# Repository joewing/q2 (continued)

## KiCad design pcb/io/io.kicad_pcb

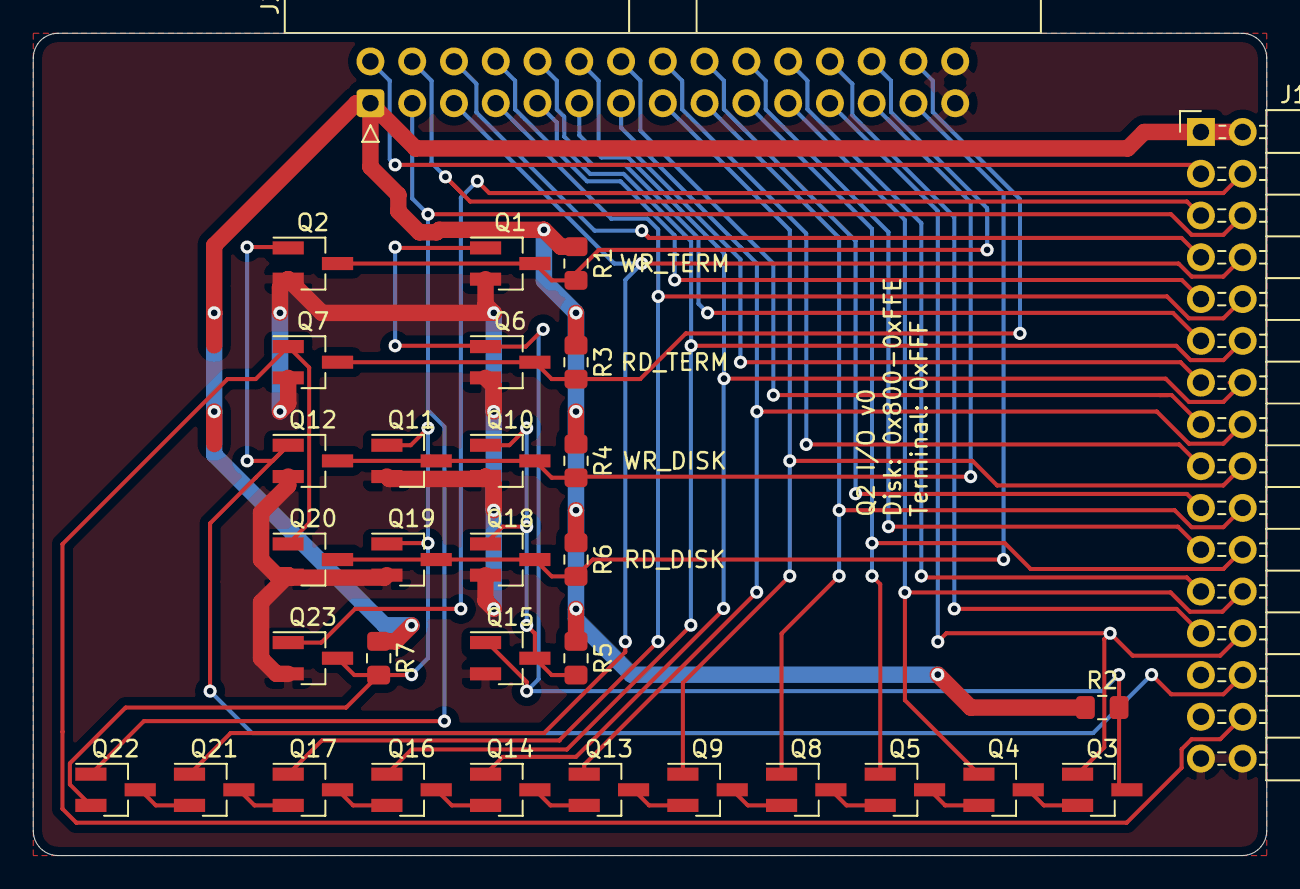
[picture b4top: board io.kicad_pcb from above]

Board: 2 copper layers, 75.0 x 50.0 mm, 32 parts (0 on the bottom side), 45 nets.

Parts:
J1: Main; PinHeader_2x16_P2.54mm_Horizontal
J2: Disk; IDC-Header_2x15_P2.54mm_Horizontal
Q1, Q2, Q3, Q4, Q5, Q6, Q7, Q8, Q9, Q10, Q11, Q12, Q13, Q14, Q15, Q16, Q17, Q18, Q19, Q20, Q21, Q22, Q23: 2N7002; SOT-23_Handsoldering
R1, R2, R3, R4, R5, R6, R7: 10k; R_0805_2012Metric_Pad1.15x1.40mm_HandSolder

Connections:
A0: J1.26, J2.23, Q3.1
A1: J1.24, J2.21, Q4.1
A2: J1.22, J2.19, Q5.1
A3: J1.20, J2.17, Q8.1
A4: J1.18, J2.15, Q9.1
A5: J1.16, J2.13, Q13.1
A6: J1.14, J2.11, Q14.1
A7: J1.12, J2.9, Q16.1
A8: J1.10, J2.7, Q17.1
A9: J1.8, J2.5, Q21.1
A10: J1.6, J2.3, Q22.1
A11: J1.4, Q23.1
D0: J1.25, J2.24
D1: J1.23, J2.22
D2: J1.21, J2.20
D3: J1.19, J2.18
D4: J1.17, J2.16
D5: J1.15, J2.14
D6: J1.13, J2.12
D7: J1.11, J2.10
D8: J1.9, J2.8
D9: J1.7, J2.6
D10: J1.5, J2.4
D11: J1.3, J2.2
GND: J1.31, J1.32, J2.29, J2.30, Q1.2, Q2.2, Q6.2, Q7.2, Q10.2, Q11.2, Q12.2, Q15.2, Q18.2, Q19.2, Q20.2, Q23.2
unnamed: Q1.1, Q3.3, Q6.1, Q15.1, R2.2
unnamed: Q3.2, Q4.3
unnamed: Q4.2, Q5.3
unnamed: Q5.2, Q8.3
unnamed: Q8.2, Q9.3
unnamed: Q10.1, Q15.3, Q18.1, R5.2
unnamed: Q13.2, Q14.3
unnamed: Q9.2, Q13.3
unnamed: Q14.2, Q16.3
unnamed: Q16.2, Q17.3
unnamed: Q17.2, Q21.3
unnamed: Q21.2, Q22.3
RD_DISK: J2.27, Q18.3, Q19.3, Q20.3, R6.2
RD_TERM: J2.28, Q6.3, Q7.3, R3.2
VCC: J1.1, J1.2, J2.1, R1.1, R2.1, R3.1, R4.1, R5.1, R6.1, R7.1
WR_DISK: J2.25, Q10.3, Q11.3, Q12.3, R4.2
WR_TERM: J2.26, Q1.3, Q2.3, R1.2
~A11: Q11.1, Q19.1, Q22.2, Q23.3, R7.2
~RDM: J1.30, Q7.1, Q20.1
~WRM: J1.28, Q2.1, Q12.1

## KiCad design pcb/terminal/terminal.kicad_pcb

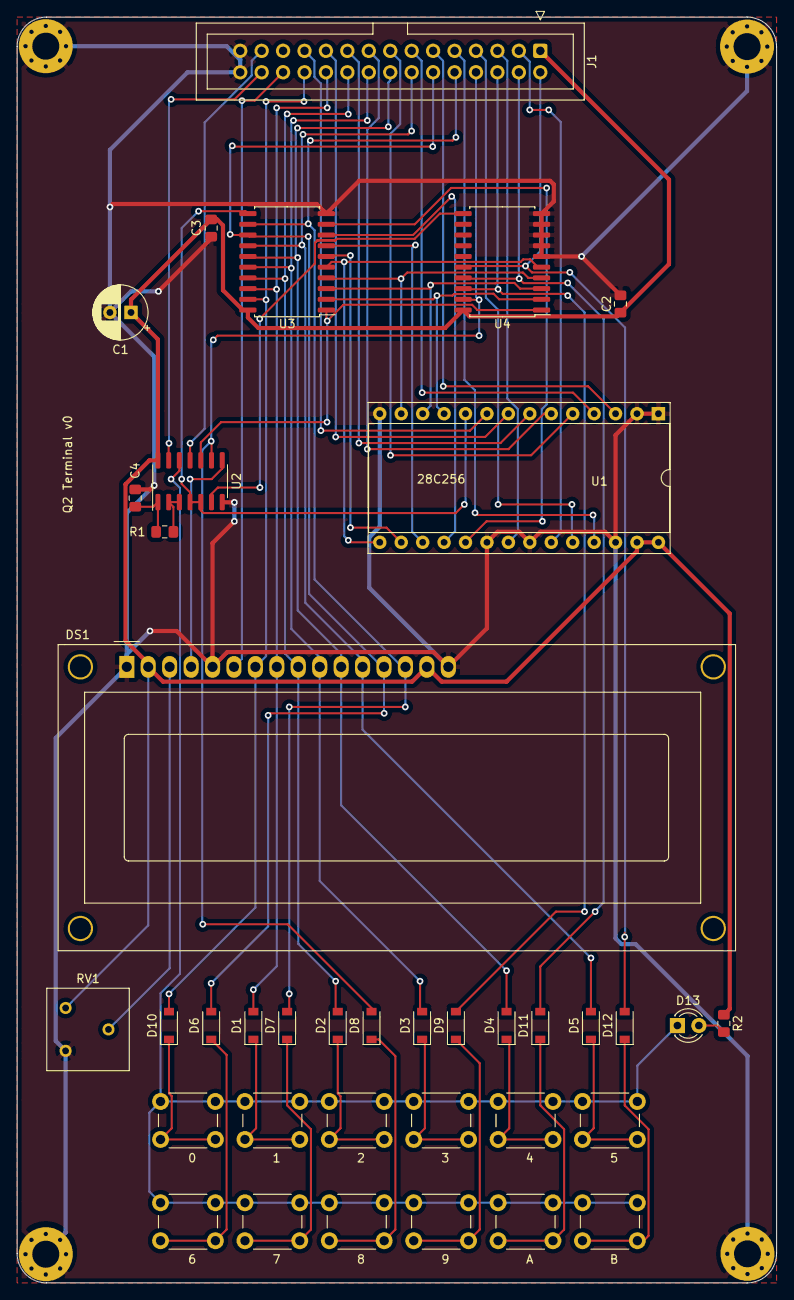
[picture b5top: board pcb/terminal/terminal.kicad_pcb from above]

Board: 2 copper layers, 90.0 x 150.0 mm, 42 parts (0 on the bottom side), 57 nets.

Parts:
C1: 47u; CP_Radial_D6.3mm_P2.50mm
C2, C3, C4: 0.1u; C_0805_2012Metric_Pad1.15x1.40mm_HandSolder
D1, D2, D3, D4, D5, D6, D7, D8, D9, D10, D11, D12: 1N4148; D_SOD-123
D13: LED; LED_D3.0mm
DS1: WC1602A
H1, H2, H3, H4: MountingHole_Pad; MountingHole_3.2mm_M3_Pad_Via
J1: Conn_02x15_Odd_Even; IDC-Header_2x15_P2.54mm_Vertical
R1: 1k; R_0805_2012Metric_Pad1.15x1.40mm_HandSolder
R2: 10k; R_0805_2012Metric_Pad1.15x1.40mm_HandSolder
RV1: 10k; Potentiometer_Bourns_3386F_Vertical
SW1: 1; SW_PUSH_6mm
SW2: 2; SW_PUSH_6mm
SW3: 3; SW_PUSH_6mm
SW4: A; SW_PUSH_6mm
SW5: 4; SW_PUSH_6mm
SW6: 5; SW_PUSH_6mm
SW7: 6; SW_PUSH_6mm
SW8: B; SW_PUSH_6mm
SW9: 7; SW_PUSH_6mm
SW10: 8; SW_PUSH_6mm
SW11: 9; SW_PUSH_6mm
SW13: 0; SW_PUSH_6mm
U1: 28C256; DIP-28_W15.24mm_Socket
U2: 14; SOIC-14_3.9x8.7mm_P1.27mm
U3, U4: 574; SOIC-20W_7.5x12.8mm_P1.27mm

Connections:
A0: J1.23, U1.9
A1: J1.21, U1.8
A2: J1.19, U1.7
A3: J1.17, U1.6
A4: J1.15, U1.5
A5: J1.13, U1.4
A6: J1.11, U1.3
A7: J1.9, U1.25
A8: J1.7, U1.24
A9: J1.5, U1.21
A10: J1.3, U1.23
D0: D10.2, DS1.7, J1.24, U3.19
D1: D1.2, DS1.8, J1.22, U3.18
D2: D2.2, DS1.9, J1.20, U3.17
D3: D3.2, DS1.10, J1.18, U3.16
D4: D4.2, DS1.11, J1.16, U3.15
D5: D5.2, DS1.12, J1.14, U3.14
D6: D6.2, DS1.13, J1.12, U3.13
D7: D7.2, DS1.14, J1.10, U3.12
D8: D8.2, J1.8, U2.9, U4.19
D9: D9.2, J1.6, U4.18
D10: D11.2, J1.4, U4.17
D11: D12.2, J1.2, U4.16
GND: C1.2, C2.2, C3.2, C4.2, DS1.1, DS1.5, DS1.16, H1.1, H2.1, H3.1, H4.1, J1.29, J1.30, RV1.1, U1.1, U1.2, U1.14, U1.20, U1.22, U1.26, U2.7, U3.10, U4.6, U4.7, U4.8, U4.9, U4.10
unnamed: C4.1, R1.1, U2.1
unnamed: D1.1, SW1.2
unnamed: D2.1, SW2.2
unnamed: D3.1, SW3.2
unnamed: D4.1, SW5.2
unnamed: D5.1, SW6.2
unnamed: D6.1, SW7.2
unnamed: D7.1, SW9.2
unnamed: D8.1, SW10.2
unnamed: D9.1, SW11.2
unnamed: D10.1, SW13.2
unnamed: D11.1, SW4.2
unnamed: D12.1, SW8.2
unnamed: D13.1, SW1.1, SW2.1, SW3.1, SW4.1, SW5.1, SW6.1, SW7.1, SW8.1, SW9.1, SW10.1, SW11.1, SW13.1, U2.12
unnamed: D13.2, R2.2
unnamed: DS1.3, RV1.2
unnamed: DS1.4, U2.8
unnamed: R1.2, U2.2, U2.3
unnamed: U1.10, U2.4, U2.5, U3.11
unnamed: U1.11, U3.2, U4.2
unnamed: U1.12, U3.3, U4.3
unnamed: U1.13, U3.4, U4.4
unnamed: U1.15, U3.5, U4.5
unnamed: U1.16, U3.6
unnamed: U1.17, U3.7
unnamed: U1.18, U3.8
unnamed: U1.19, U3.9
unnamed: U2.6, U4.11
unnamed: U2.10, U3.1, U4.1
RD_DISK: J1.27, U2.11
RD_TERM: J1.28, U2.13
VCC: C1.1, C2.1, C3.1, DS1.2, DS1.15, J1.1, R2.1, RV1.3, U1.27, U1.28, U2.14, U3.20, U4.20
WR_TERM: DS1.6, J1.26

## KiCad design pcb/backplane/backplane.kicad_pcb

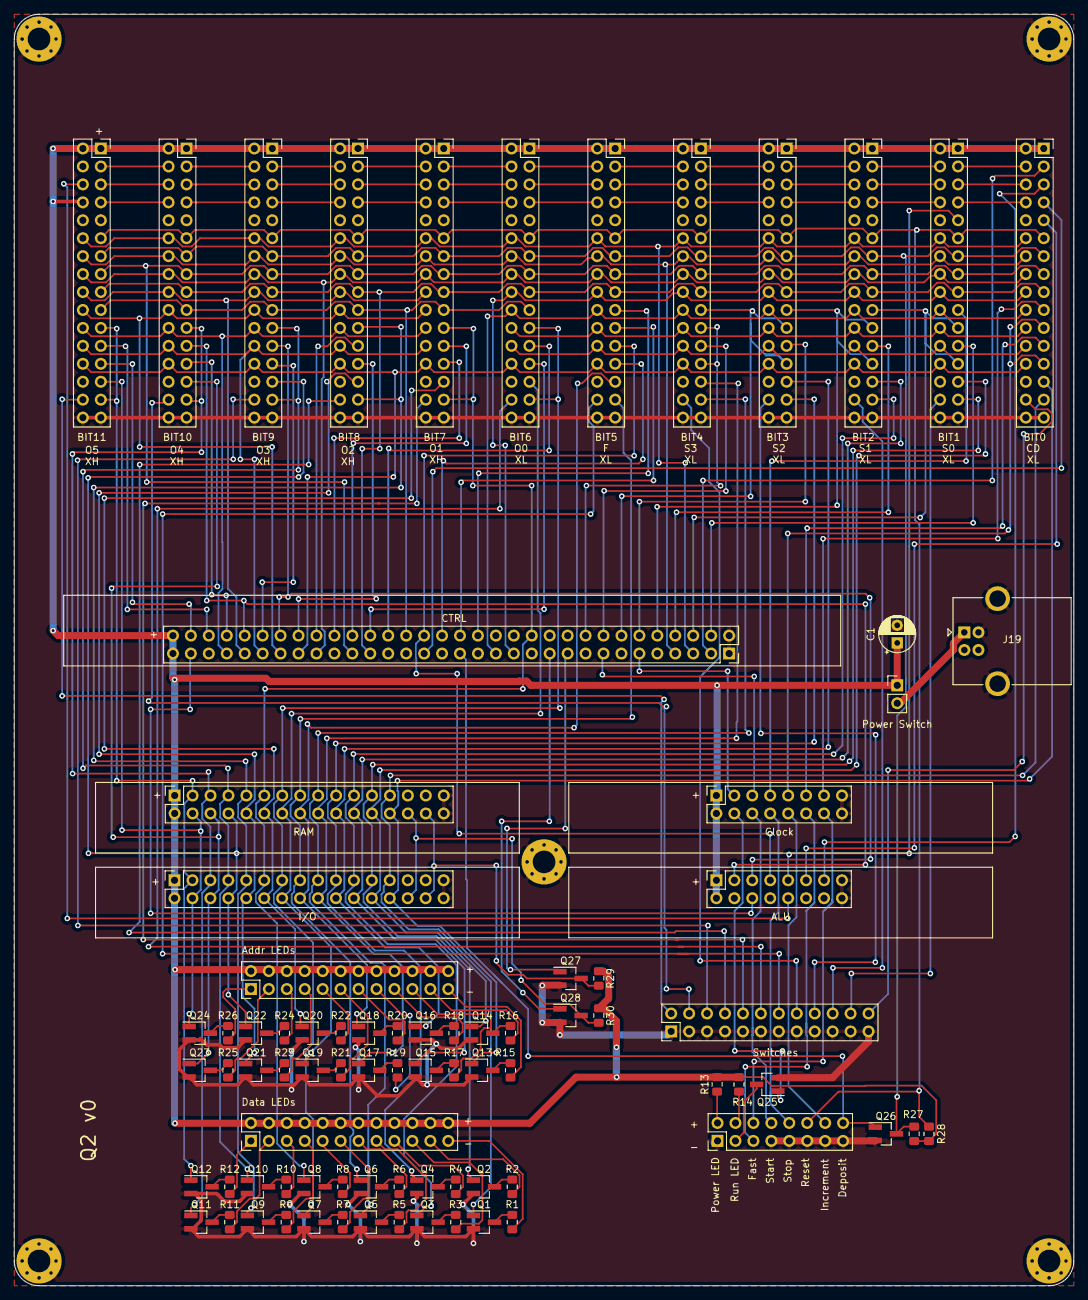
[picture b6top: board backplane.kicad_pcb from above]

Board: 2 copper layers, 150.0 x 180.0 mm, 87 parts (0 on the bottom side), 188 nets.

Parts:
C1: 47u; CP_Radial_D5.0mm_P2.50mm
H1, H2, H3, H4, H5: MountingHole_Pad; MountingHole_3.2mm_M3_Pad_Via
J1: BIT11; PinSocket_2x16_P2.54mm_Vertical
J2: BIT10; PinSocket_2x16_P2.54mm_Vertical
J3: BIT9; PinSocket_2x16_P2.54mm_Vertical
J4: BIT8; PinSocket_2x16_P2.54mm_Vertical
J5: BIT7; PinSocket_2x16_P2.54mm_Vertical
J6: BIT6; PinSocket_2x16_P2.54mm_Vertical
J7: BIT5; PinSocket_2x16_P2.54mm_Vertical
J8: BIT4; PinSocket_2x16_P2.54mm_Vertical
J9: BIT3; PinSocket_2x16_P2.54mm_Vertical
J10: BIT2; PinSocket_2x16_P2.54mm_Vertical
J11: BIT1; PinSocket_2x16_P2.54mm_Vertical
J12: BIT0; PinSocket_2x16_P2.54mm_Vertical
J13: CTRL; PinSocket_2x32_P2.54mm_Vertical
J14: ALU; PinSocket_2x08_P2.54mm_Vertical
J15: Clock; PinSocket_2x08_P2.54mm_Vertical
J16: RAM; PinSocket_2x16_P2.54mm_Vertical
J17: I/O; PinSocket_2x16_P2.54mm_Vertical
J18: Power Switch; PinHeader_1x02_P2.54mm_Vertical
J19: USB_B; USB_B_OST_USB-B1HSxx_Horizontal
J20: Control Switches; PinHeader_2x08_P2.54mm_Vertical
J21: Data LEDs; PinHeader_2x12_P2.54mm_Vertical
J22: Addr LEDs; PinHeader_2x12_P2.54mm_Vertical
J23: Switches; PinHeader_2x12_P2.54mm_Vertical
Q1, Q2, Q3, Q4, Q5, Q6, Q7, Q8, Q9, Q10, Q11, Q12, Q13, Q14, Q15, Q16, Q17, Q18, Q19, Q20, Q21, Q22, Q23, Q24, Q25, Q26, Q27, Q28: 2N7002; SOT-23_Handsoldering
R1, R2, R3, R4, R5, R6, R7, R8, R9, R10, R11, R12, R13, R14, R15, R16, R17, R18, R19, R20, R21, R22, R23, R24, R25, R26, R27, R28, R29, R30: 10k; R_0805_2012Metric_Pad1.15x1.40mm_HandSolder

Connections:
/A1: J11.5, J12.6
/A2: J10.5, J11.6
/A3: J9.5, J10.6
/A4: J8.5, J9.6
/A5: J7.5, J8.6
/P4: J7.3, J8.4
/~P0: J11.3, J12.4
/~P1: J10.3, J11.4
/~P2: J9.3, J10.4
/~P3: J8.3, J9.4
/~X1: J11.7, J12.8
/~X2: J10.7, J11.8
/~X3: J9.7, J10.8
/~X4: J8.7, J9.8
/~X5: J7.7, J8.8
A0: J12.5, J14.13
A0_LED: J22.23, R15.1
A1_LED: J22.21, R16.1
A2_LED: J22.19, R17.1
A3_LED: J22.17, R18.1
A4_LED: J22.15, R19.1
A5_LED: J22.13, R20.1
A6_LED: J22.11, R21.1
A7_LED: J22.9, R22.1
A8_LED: J22.7, R23.1
A9_LED: J22.5, R24.1
A10_LED: J22.3, R25.1
A11_LED: J22.1, R26.1
ABUS0: J12.27, J16.26, J17.26, Q13.1
ABUS1: J11.27, J16.24, J17.24, Q14.1
ABUS2: J10.27, J16.22, J17.22, Q15.1
ABUS3: J9.27, J16.20, J17.20, Q16.1
ABUS4: J8.27, J16.18, J17.18, Q17.1
ABUS5: J7.27, J16.16, J17.16, Q18.1
ABUS6: J6.27, J16.14, J17.14, Q19.1
ABUS7: J5.27, J16.12, J17.12, Q20.1
ABUS8: J4.27, J16.10, J17.10, Q21.1
ABUS9: J3.27, J16.8, J17.8, Q22.1
ABUS10: J2.27, J16.6, J17.6, Q23.1
ABUS11: J1.27, J16.4, J17.4, Q24.1
ALU_OUT: J1.6, J14.10
CDIV: J12.23, J15.11
CLK: J12.19, J15.13
D0_LED: J21.23, R1.1
D1_LED: J21.21, R2.1
D2_LED: J21.19, R3.1
D3_LED: J21.17, R4.1
D4_LED: J21.15, R5.1
D5_LED: J21.13, R6.1
D6_LED: J21.11, R7.1
D7_LED: J21.9, R8.1
D8_LED: J21.7, R9.1
D9_LED: J21.5, R10.1
D10_LED: J21.3, R11.1
D11_LED: J21.1, R12.1
DBUS0: J12.29, J16.25, J17.25, Q1.1
DBUS1: J11.29, J16.23, J17.23, Q2.1
DBUS2: J10.29, J16.21, J17.21, Q3.1
DBUS3: J9.29, J16.19, J17.19, Q4.1
DBUS4: J8.29, J16.17, J17.17, Q5.1
DBUS5: J7.29, J16.15, J17.15, Q6.1
DBUS6: J6.21, J6.29, J16.13, J17.13, Q7.1
DBUS7: J5.21, J5.29, J13.24, J16.11, J17.11, Q8.1
DBUS8: J4.21, J4.29, J16.9, J17.9, Q9.1
DBUS9: J3.21, J3.29, J16.7, J17.7, Q10.1
DBUS10: J2.21, J2.29, J16.5, J17.5, Q11.1
DBUS11: J1.21, J1.29, J16.3, J17.3, Q12.1
DEP: J1.13, J2.13, J3.13, J4.13, J5.13, J6.13, J7.13, J8.13, J9.13, J10.13, J11.13, J12.13, Q26.3, R27.2
F: J7.23, J13.36, J14.7
FAST_IN: J15.14, J20.6
FAST_OUT: J15.12, J20.5
GND: C1.2, H1.1, H2.1, H3.1, H4.1, H5.1, J1.31, J1.32, J2.31, J2.32, J3.31, J3.32, J4.31, J4.32, J5.31, J5.32, J6.31, J6.32, J7.31, J7.32, J8.31, J8.32, J9.31, J9.32, J10.31, J10.32, J11.31, J11.32, J12.31, J12.32, J13.1, J13.2, J14.15, J14.16, J15.15, J15.16, J16.31, J16.32, J17.31, J17.32, J19.4, J19.5, J20.1, J20.7, J20.9, J20.11, J20.13, J20.15, J23.1, J23.3, J23.5, J23.7, J23.9, J23.11, J23.13, J23.15, J23.17, J23.19, J23.21, J23.23, Q1.2, Q2.2, Q3.2, Q4.2, Q5.2, Q6.2, Q7.2, Q8.2, Q9.2, Q10.2, Q11.2, Q12.2, Q13.2, Q14.2, Q15.2, Q16.2, Q17.2, Q18.2, Q19.2, Q20.2, Q21.2, Q22.2, Q23.2, Q24.2, Q25.2, Q26.2, Q27.2, Q28.2
INCP_CLK: J12.3, J13.3
INCP_DB: J13.15, J15.5
NEXTF: J7.21, J13.32
unnamed: J1.3, J2.4
unnamed: J1.5, J2.6
unnamed: J1.7, J2.8
unnamed: J2.3, J3.4
unnamed: J2.5, J3.6
unnamed: J2.7, J3.8
unnamed: J3.3, J4.4
unnamed: J3.5, J4.6
unnamed: J3.7, J4.8
unnamed: J4.3, J5.4
unnamed: J4.5, J5.6
unnamed: J4.7, J5.8
unnamed: J5.3, J6.4
unnamed: J5.5, J6.6
unnamed: J5.7, J6.8
unnamed: J6.3, J7.4
unnamed: J6.5, J7.6
unnamed: J6.7, J7.8
unnamed: J18.2, J19.1
unnamed: J20.2, R13.2
unnamed: J20.3, Q25.3
unnamed: J20.4, R14.2
unnamed: Q1.3, R1.2
unnamed: Q2.3, R2.2
unnamed: Q3.3, R3.2
unnamed: Q4.3, R4.2
unnamed: Q5.3, R5.2
unnamed: Q6.3, R6.2
unnamed: Q7.3, R7.2
unnamed: Q8.3, R8.2
unnamed: Q9.3, R9.2
unnamed: Q10.3, R10.2
unnamed: Q11.3, R11.2
unnamed: Q12.3, R12.2
unnamed: Q13.3, R15.2
unnamed: Q14.3, R16.2
unnamed: Q15.3, R17.2
unnamed: Q16.3, R18.2
unnamed: Q17.3, R19.2
unnamed: Q18.3, R20.2
unnamed: Q19.3, R21.2
unnamed: Q20.3, R22.2
unnamed: Q21.3, R23.2
unnamed: Q22.3, R24.2
unnamed: Q23.3, R25.2
unnamed: Q24.3, R26.2
OP0: J6.23, J13.40
OP1: J5.23, J13.44
OP2: J4.23, J13.48
OP3: J3.23, J13.52, J14.5
OP4: J2.23, J13.56, J14.3
OP5: J1.23, J13.60
RDA_DBUS: J1.15, J2.15, J3.15, J4.15, J5.15, J6.15, J7.15, J8.15, J9.15, J10.15, J11.15, J12.15, J13.43
RDM: J13.19, Q27.1
RDP_ABUS: J1.14, J2.14, J3.14, J4.14, J5.14, J6.14, J7.14, J8.14, J9.14, J10.14, J11.14, J12.14, J13.7
RDX_ABUS: J1.16, J2.16, J3.16, J4.16, J5.16, J6.16, J7.16, J8.16, J9.16, J10.16, J11.16, J12.16, J13.47
RUN: J15.4, Q25.1
S0: J11.23, J13.4
S1: J10.23, J13.8
S2: J9.23, J13.12
S3: J8.23, J13.16
SC: J11.19, J15.7
VCC: C1.1, J1.1, J1.2, J1.8, J2.1, J2.2, J3.1, J3.2, J4.1, J4.2, J5.1, J5.2, J6.1, J6.2, J7.1, J7.2, J8.1, J8.2, J9.1, J9.2, J10.1, J10.2, J11.1, J11.2, J12.1, J12.2, J13.63, J13.64, J14.1, J14.2, J15.1, J15.2, J16.1, J16.2, J17.1, J17.2, J18.1, J21.2, J21.4, J21.6, J21.8, J21.10, J21.12, J21.14, J21.16, J21.18, J21.20, J21.22, J21.24, J22.2, J22.4, J22.6, J22.8, J22.10, J22.12, J22.14, J22.16, J22.18, J22.20, J22.22, J22.24, R13.1, R14.1, R27.1, R28.1, R29.1, R30.1
WRA: J1.17, J2.17, J3.17, J4.17, J5.17, J6.17, J7.17, J8.17, J9.17, J10.17, J11.17, J12.17, J13.41
WRF: J7.19, J13.30
WRM: J13.21, Q28.1
WRO: J1.19, J2.19, J3.19, J4.19, J5.19, J6.19, J13.38
WRX: J1.26, J2.26, J3.26, J4.26, J5.26, J6.26, J7.26, J8.26, J9.26, J10.26, J11.26, J12.26, J13.49
WS: J13.11, J15.3
X0: J12.9, J14.11
X1: J11.9, J14.9
XHIN_DBUS: J1.18, J2.18, J3.18, J4.18, J5.18, J13.55
XHIN_P: J1.22, J2.22, J3.22, J4.22, J5.22, J13.57
XHIN_SHIFT: J1.20, J2.20, J3.20, J4.20, J5.20, J13.51
XHIN_ZERO: J1.24, J2.24, J3.24, J4.24, J5.24, J13.53
XLIN_DBUS: J6.18, J7.18, J8.18, J9.18, J10.18, J11.18, J12.18, J13.25
XLIN_P: J6.22, J7.22, J8.22, J9.22, J10.22, J11.22, J12.22
XLIN_SHIFT: J6.20, J7.20, J8.20, J9.20, J10.20, J11.20, J12.20, J13.27
XLIN_ZERO: J6.24, J7.24, J8.24, J9.24, J10.24, J11.24, J12.24
~ALU_COUT: J13.61, J14.6
~CDIV: J12.21, J12.25, J15.9
~DEP_SW: J13.31, J20.16, Q26.1
~F: J7.25, J13.34
~INCP_SW: J15.10, J20.14
~OP0: J6.25, J13.42
~OP1: J5.25, J13.46
~OP2: J4.25, J13.50
~OP3: J3.25, J13.54
~OP4: J2.25, J13.58
~OP5: J1.25, J13.62
~RDM: J16.30, J17.30, Q27.3, R29.2
~RST: J1.11, J2.11, J3.11, J4.11, J5.11, J6.11, J7.11, J8.11, J9.11, J10.11, J11.11, J12.11, J20.12, R28.2
~S0: J10.19, J11.21, J11.25, J13.6
~S1: J9.19, J10.21, J10.25, J13.10
~S2: J8.19, J9.21, J9.25, J13.14
~S3: J8.21, J8.25, J13.18
~START_SW: J15.6, J20.8
~STOP_SW: J15.8, J20.10
~SW0: J12.30, J23.24
~SW1: J11.30, J23.22
~SW2: J10.30, J23.20
~SW3: J9.30, J23.18
~SW4: J8.30, J23.16
~SW5: J7.30, J23.14
~SW6: J6.30, J23.12
~SW7: J5.30, J23.10
~SW8: J4.30, J23.8
~SW9: J3.30, J23.6
~SW10: J2.30, J23.4
~SW11: J1.30, J23.2
~WRM: J16.28, J17.28, Q28.3, R30.2
~WRP: J1.12, J2.12, J3.12, J4.12, J5.12, J6.12, J7.12, J8.12, J9.12, J10.12, J11.12, J12.12, J13.5
~X0: J12.7, J13.35

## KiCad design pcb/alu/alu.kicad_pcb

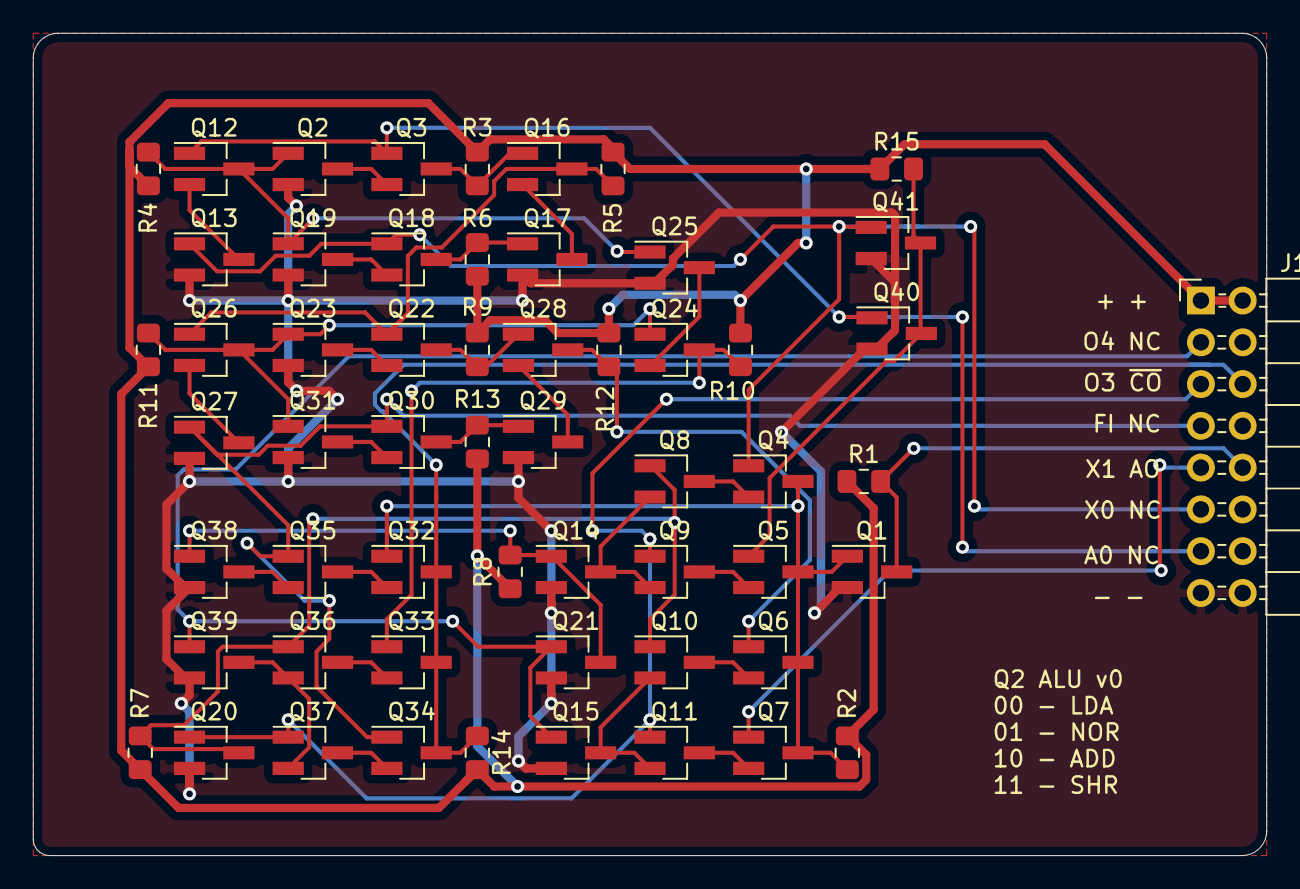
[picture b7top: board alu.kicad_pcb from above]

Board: 2 copper layers, 75.0 x 50.0 mm, 57 parts (0 on the bottom side), 43 nets.

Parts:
J1: Conn_02x08_Odd_Even; PinHeader_2x08_P2.54mm_Horizontal
Q1, Q2, Q3, Q4, Q5, Q6, Q7, Q8, Q9, Q10, Q11, Q12, Q13, Q14, Q15, Q16, Q17, Q18, Q19, Q20, Q21, Q22, Q23, Q24, Q25, Q26, Q27, Q28, Q29, Q30, Q31, Q32, Q33, Q34, Q35, Q36, Q37, Q38, Q39, Q40, Q41: 2N7002; SOT-23_Handsoldering
R1, R2, R3, R4, R5, R6, R7, R8, R9, R10, R11, R12, R13, R14, R15: R; R_0805_2012Metric_Pad1.15x1.40mm_HandSolder

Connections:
A0: J1.13, Q3.1, Q12.1, Q40.1
ALU_NOR: Q5.1, Q40.3, Q41.3, R15.2
ALU_OUT: J1.10, Q1.3, R1.2
ALU_SUM: Q6.1, Q28.3, R12.2
F: J1.7, Q27.1, Q30.1, Q34.1, Q35.1
GND: J1.15, J1.16, Q1.2, Q2.2, Q13.2, Q14.2, Q15.2, Q17.2, Q19.2, Q20.2, Q21.2, Q23.2, Q25.2, Q27.2, Q29.2, Q31.2, Q38.2, Q39.2, Q40.2, Q41.2
unnamed: Q2.3, Q3.2
unnamed: Q4.2, Q8.3
unnamed: Q5.2, Q9.3
unnamed: Q10.2, Q11.2, Q15.3
unnamed: Q6.2, Q10.3
unnamed: Q7.2, Q11.3
unnamed: Q12.2, Q13.3
unnamed: Q2.1, Q12.3, Q19.1, Q25.1, R4.2
unnamed: Q8.2, Q9.2, Q14.3
unnamed: Q3.3, Q16.1, R3.2
unnamed: Q16.2, Q17.3
unnamed: Q16.3, Q22.1, Q26.1, R5.2
unnamed: Q17.1, Q18.3, R6.2
unnamed: Q18.2, Q19.3
unnamed: Q22.2, Q23.3
unnamed: Q22.3, Q28.1, R9.2
unnamed: Q23.1, Q24.1, Q26.3, Q31.1, R11.2
unnamed: Q24.2, Q25.3
unnamed: Q24.3, Q33.1, R10.2
unnamed: Q26.2, Q27.3
unnamed: Q28.2, Q29.3
unnamed: Q29.1, Q30.3, R13.2
unnamed: Q30.2, Q31.3
unnamed: Q32.2, Q35.3
unnamed: Q33.2, Q36.3
unnamed: Q34.2, Q37.3
unnamed: Q35.2, Q38.3
unnamed: Q36.2, Q37.2, Q39.3
OP3: J1.5, Q9.1, Q11.1, Q20.1, Q37.1
OP4: J1.3, Q15.1, Q21.1, Q39.1
VCC: J1.1, J1.2, R1.1, R2.1, R3.1, R4.1, R5.1, R6.1, R7.1, R8.1, R9.1, R10.1, R11.1, R12.1, R13.1, R14.1, R15.1
X0: J1.11, Q4.1, Q13.1, Q18.1, Q41.1
X1: J1.9, Q7.1
~ALU_COUT: J1.6, Q32.3, Q33.3, Q34.3, R14.2
~ALU_OUT: Q1.1, Q4.3, Q5.3, Q6.3, Q7.3, Q32.1, R2.2
~OP3: Q8.1, Q10.1, Q20.3, Q36.1, R7.2
~OP4: Q14.1, Q21.3, Q38.1, R8.2

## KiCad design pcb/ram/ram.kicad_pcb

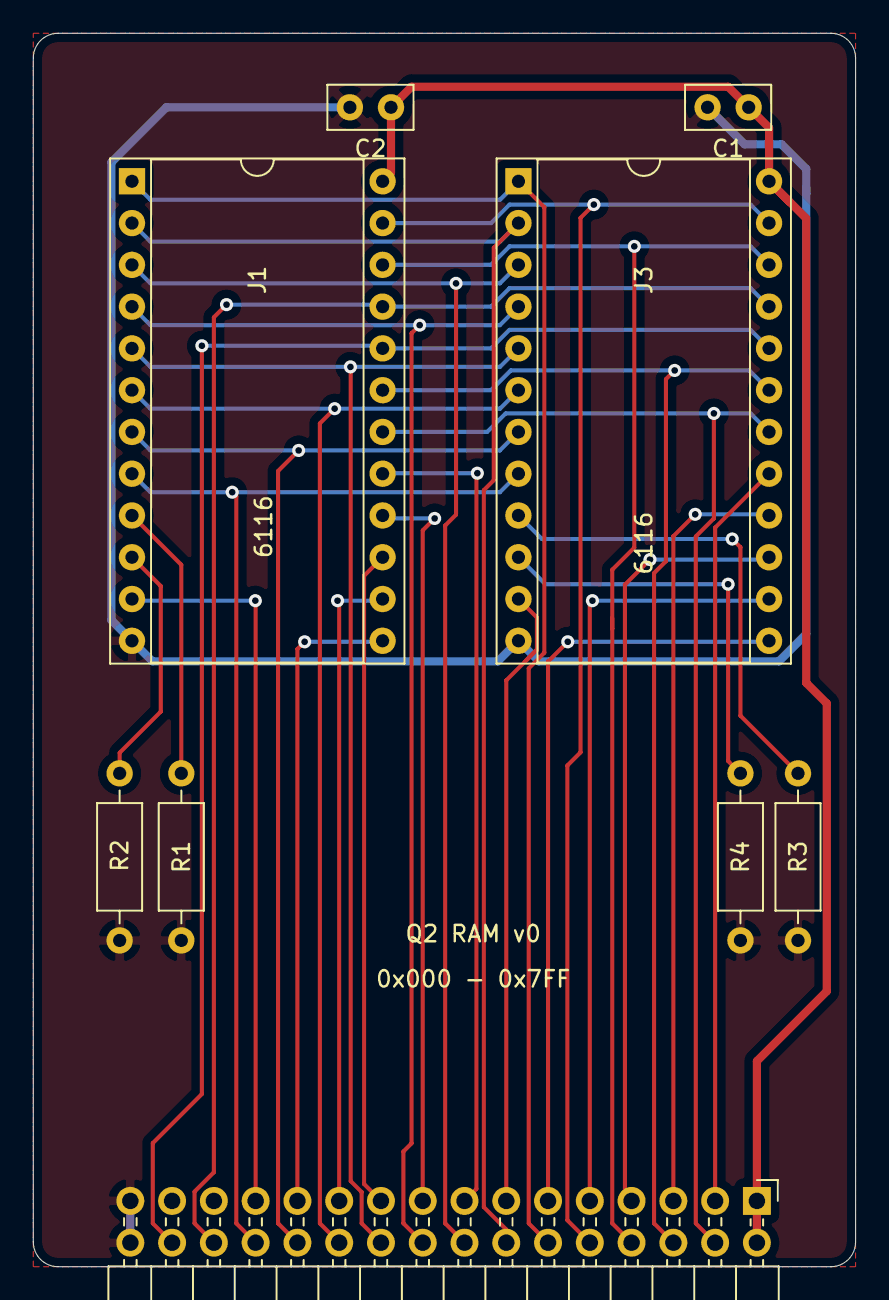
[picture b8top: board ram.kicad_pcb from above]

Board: 2 copper layers, 50.0 x 75.0 mm, 9 parts (0 on the bottom side), 32 nets.

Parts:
C1, C2: 0.1u; C_Disc_D5.0mm_W2.5mm_P2.50mm
J1, J3: 6116; DIP-24_W15.24mm_Socket
J2: Conn_02x16_Odd_Even; PinHeader_2x16_P2.54mm_Horizontal
R1, R2, R3, R4: 10k; R_Axial_DIN0207_L6.3mm_D2.5mm_P10.16mm_Horizontal

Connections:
A0: J1.8, J2.26, J3.8
A1: J1.7, J2.24, J3.7
A2: J1.6, J2.22, J3.6
A3: J1.5, J2.20, J3.5
A4: J1.4, J2.18, J3.4
A5: J1.3, J2.16, J3.3
A6: J1.2, J2.14, J3.2
A7: J1.1, J2.12, J3.1
A8: J1.23, J2.10, J3.23
A9: J1.22, J2.8, J3.22
A10: J1.19, J2.6, J3.19
A11: J1.18, J2.4, J3.18
D0: J1.11, J2.25
D1: J1.13, J2.23
D2: J1.14, J2.21
D3: J1.15, J2.19
D4: J1.16, J2.17
D5: J1.17, J2.15
D6: J2.13, J3.11
D7: J2.11, J3.13
D8: J2.9, J3.14
D9: J2.7, J3.15
D10: J2.5, J3.16
D11: J2.3, J3.17
GND: C1.2, C2.2, J1.12, J2.31, J2.32, J3.12, R1.2, R2.2, R3.2, R4.2
unnamed: J1.9, R1.1
unnamed: J1.10, R2.1
unnamed: J3.9, R3.1
unnamed: J3.10, R4.1
VCC: C1.1, C2.1, J1.24, J2.1, J2.2, J3.24
~RDM: J1.20, J2.30, J3.20
~WRM: J1.21, J2.28, J3.21

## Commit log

2020-03-15 First commit.
2020-03-15 q2asm
2020-03-22 q2sim and q2asm updates.
2020-03-22 isqrt example
2020-05-13 Commit before simplification.
2020-09-13 New design
2020-09-14 More routing.
2020-09-15 Updates.
2020-09-19 Signed immediates.
2020-09-19 No load flag.
2020-09-20 Schematic updates.
2020-09-21 RAM board
2020-09-22 More stuff.
2020-09-29 Add some assembler directives.
2020-10-03 Fixes
2020-10-05 Terminal
2020-10-24 More fixes
2021-02-07 Start v2.
    More stuff.
    More stuff.
2021-02-07 Routed
2021-02-07 v2 PCB.
2021-02-07 Smaller
2021-02-07 Cleanups.
2021-02-13 Pi programmer.
2021-02-14 Move pins around.
2021-02-15 Move pins some more.
2021-02-16 One more pin.
2021-02-23 Buttons.
2021-02-23 Bit low/high.
2021-02-23 XH/XL.
2021-02-23 Fewer transistors.
2021-02-23 Relink.
2021-02-24 Annotate.
2021-02-26 Checkpoint.
2021-02-27 Fix UUIDs.
2021-02-28 New reset.
2021-03-01 Skip ALU state for jfc/jmp/sta.
2021-03-07 Some fixes.
2021-03-09 Faster.
2021-03-13 Update resistors.
2021-03-13 Renames.
2021-03-14 Fix flag for lea.
2021-03-15 Revision 3.
2021-03-22 Snake.
2021-03-23 Better.
2021-03-26 q2prog updates.
2021-03-26 Updates for new hardware.
2021-04-05 Fix case.
2021-04-10 Start I2C interface.
2021-04-10 Start at 000
2021-04-10 Move stuff.
2021-04-17 Pong game.
2021-04-18 Floating point.
2021-05-10 Start rev4.
2021-08-02 Routed.
2021-08-11 I2C updates.
2021-09-25 More updates.
2021-09-28 Update.
2021-10-06 Immediate mode.
2021-10-09 Timing updates.
2021-10-16 Compiler.
2021-10-16 More builtins.
2021-10-17 Simplify
2021-10-17 Add stuff.
2021-10-24 Custom parser.
2021-10-25 Better error checking.
2021-10-31 Nested functions.
2021-11-07 Memory extension.
2022-02-13 Rule to build q2lc.
2022-02-13 Invaders game.
2022-02-19 Image.
2022-02-27 Some new examples.
2022-02-27 Fixes.
2022-03-05 Another fix.
2022-03-12 New oscillator.
2022-03-13 Routing.
2022-03-14 Save.
2022-03-19 Some updates/fixes.
2022-03-20 More efficient.
2022-03-26 Add q2prog reset action.
2022-04-03 Some updates.
2022-04-03 I2C fix.
2022-04-16 Better decoupling.
2022-05-07 KiCad 6.
2022-06-10 Routing updates.
2022-10-11 PCB fixes/updates.
2022-11-10 Add gerber files.
2024-12-15 q2lc fixes
2024-12-15 Board updates.
